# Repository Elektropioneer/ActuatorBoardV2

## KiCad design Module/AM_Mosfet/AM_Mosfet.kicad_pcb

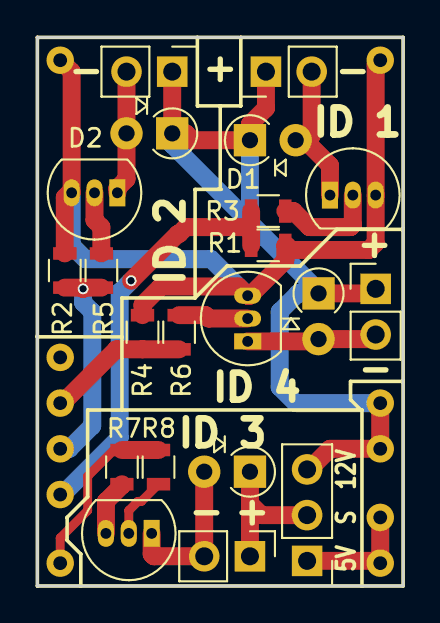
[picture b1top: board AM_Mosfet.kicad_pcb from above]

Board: 2 copper layers, 20.3 x 30.5 mm, 22 parts (0 on the bottom side), 16 nets.

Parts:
D1, D2, D3, D4: D; D_A-405_P2.54mm_Vertical_AnodeUp
J1, J2, J3, J5: CONN_01X02; Pin_Header_Straight_1x02_Pitch2.54mm
J4: CONN_01X03; Pin_Header_Straight_1x03_Pitch2.54mm
M1: Aktuator_Module
Q1, Q2, Q3, Q4: BS170; TO-92_Inline_Narrow_Oval
R1, R2, R4, R7: 10K; R_0805
R3, R5, R6, R8: 1K; R_0805

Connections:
+5V: J4.1, M1.1
+12V: D1.1, D2.1, D4.1, J1.1, J2.1, J3.1, J4.3, M1.2
GND: M1.4, Q1.3, Q2.3, Q3.3, Q4.3, R1.2, R2.2, R4.2, R7.2
MOS_1: M1.6, R1.1, R3.2
MOS_2: M1.7, R2.1, R5.2
MOS_3: M1.3, R7.1, R8.2
MOS_4: M1.8, R4.1, R6.2
unnamed: D1.2, J2.2, Q1.1
unnamed: D2.2, J3.2, Q2.1
unnamed: D3.1, J4.2, J5.1
unnamed: D3.2, J5.2, Q3.1
unnamed: D4.2, J1.2, Q4.1
unnamed: Q1.2, R3.1
unnamed: Q2.2, R5.1
unnamed: Q3.2, R8.1
unnamed: Q4.2, R6.1
